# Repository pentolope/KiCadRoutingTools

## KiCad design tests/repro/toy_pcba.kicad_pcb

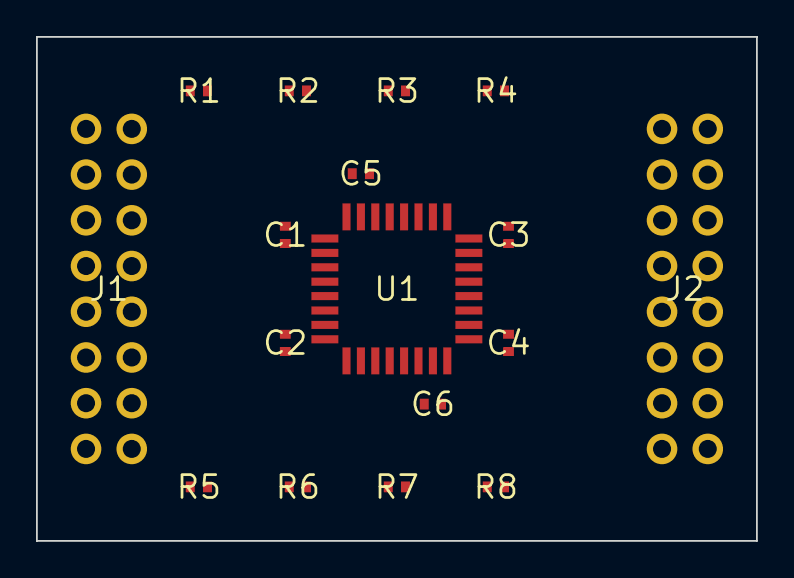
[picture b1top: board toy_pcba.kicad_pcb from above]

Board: 2 copper layers, 40.0 x 28.0 mm, 17 parts (0 on the bottom side), 26 nets, no tracks yet.

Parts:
C1, C2, C3, C4, C5, C6: 100nF
J1, J2: Conn_02x08
R1, R2, R3, R4, R5, R6, R7, R8: 33R
U1: TQFP-32

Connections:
+3V3: C1.1, C2.1, C3.1, C4.1, C5.1, C6.1, J1.2, J2.2, U1.8, U1.16, U1.24, U1.32
GND: C1.2, C2.2, C3.2, C4.2, C5.2, C6.2, J1.1, J2.1, U1.1, U1.9, U1.17, U1.25
SIG_L0: J1.3, R1.1
SIG_L1: J1.5, R2.1
SIG_L2: J1.7, R3.1
SIG_L3: J1.9, R4.1
SIG_L4: J1.11, R5.1
SIG_L5: J1.13, R6.1
SIG_L6: J1.15, R7.1
SIG_L7: J1.16, R8.1
SIG_LR0: R1.2, U1.11
SIG_LR1: R2.2, U1.10
SIG_LR2: R3.2, U1.7
SIG_LR3: R4.2, U1.6
SIG_LR4: R5.2, U1.5
SIG_LR5: R6.2, U1.4
SIG_LR6: R7.2, U1.3
SIG_LR7: R8.2, U1.2
SIG_R0: J2.3, U1.27
SIG_R1: J2.5, U1.26
SIG_R2: J2.7, U1.23
SIG_R3: J2.9, U1.22
SIG_R4: J2.11, U1.21
SIG_R5: J2.13, U1.20
SIG_R6: J2.15, U1.19
SIG_R7: J2.16, U1.18
